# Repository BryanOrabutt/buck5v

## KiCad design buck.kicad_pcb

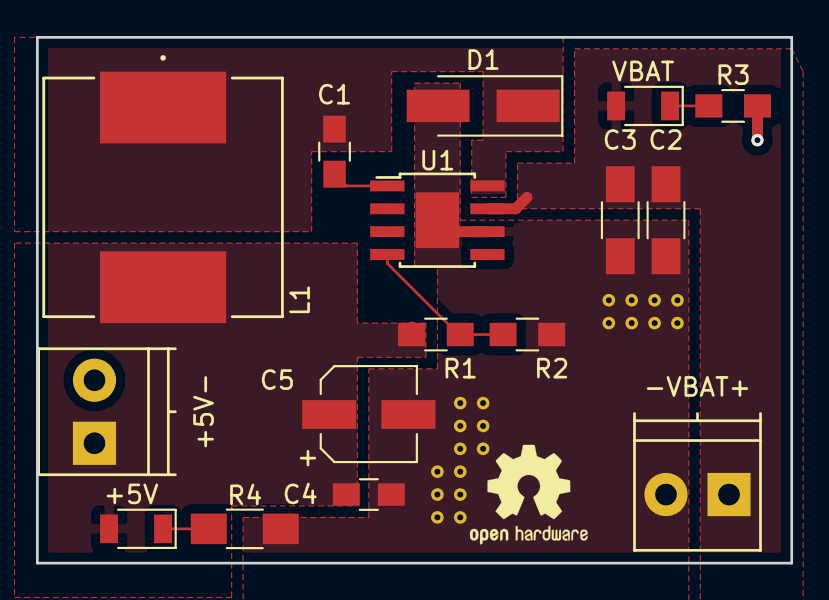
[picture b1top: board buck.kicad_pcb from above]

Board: 2 copper layers, 41.9 x 29.2 mm, 16 parts (0 on the bottom side), 8 nets.

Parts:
+5V: LED; D_1206
+5V-: -5V+; TerminalBlock_Pheonix_PT-3.5mm_2pol
-VBAT+: -VBAT+; TerminalBlock_Pheonix_PT-3.5mm_2pol
C1: 10nF; C_0805_HandSoldering
C2, C3: 4.7uF; C_1206_HandSoldering
C4: 100nF; C_0805_HandSoldering
C5: 220uF; CP_Elec_5x5.3
D1: STPS5L60U; D_SMA_Handsoldering
L1: 22uH; SRR1208-220ML
R1: 30.9K±0.1%; R_0805_HandSoldering
R2: 10K±0.1%; R_0805_HandSoldering
R3: 2K; R_0805_HandSoldering
R4: 220; R_1206_HandSoldering
U1: TPS5430; TI_SO-PowerPAD-8
VBAT: LED; D_1206

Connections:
+5V: +5V.2, +5V-.1, C4.1, C5.1, L1.2, R1.1
+BATT: -VBAT+.1, C2.1, C3.1, U1.7, VBAT.2
/PH: C1.2, D1.1, L1.1, U1.8
GND: +5V-.2, -VBAT+.2, C2.2, C3.2, C4.2, C5.2, D1.2, R2.2, R3.2, R4.2, U1.6, U1.9
unnamed: C1.1, U1.1
unnamed: R3.1, VBAT.1
unnamed: +5V.1, R4.1
unnamed: R1.2, R2.1, U1.4

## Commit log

2022-09-26 Adding project files

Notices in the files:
parts and their libraries:
Copyright 2016 Accelerated Designs. All rights reserved.
